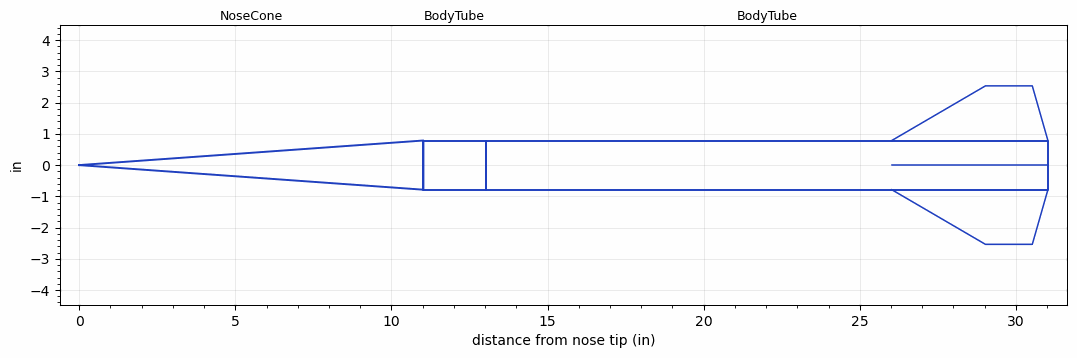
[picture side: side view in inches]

<RASAeroDocument>
 <FileVersion>2</FileVersion>
 <RocketDesign>
  <NoseCone>
   <Length>11.025</Length>
   <Diameter>1.575</Diameter>
   <Shape>Conical</Shape>
   <BluntRadius>0.065</BluntRadius>
   <Location>0</Location>
  </NoseCone>
  <BodyTube>
   <Length>2</Length>
   <Diameter>1.575</Diameter>
   <Location>11.025</Location>
  </BodyTube>
  <BodyTube>
   <Length>18</Length>
   <Diameter>1.575</Diameter>
   <Location>13.025</Location>
   <Fin>
    <Count>4</Count>
    <Chord>5</Chord>
    <Span>1.75</Span>
    <SweepDistance>3</SweepDistance>
    <TipChord>1.5</TipChord>
    <Thickness>0.1181</Thickness>
    <LERadius>0.065</LERadius>
    <Location>5</Location>
    <AirfoilSection>Hexagonal</AirfoilSection>
    <FX1>0.25</FX1>
    <FX3>0.25</FX3>
   </Fin>
   <Protuberance>
    <StreamlinedNoBaseDrag>0</StreamlinedNoBaseDrag>
    <StreamlinedWithBaseDrag>0.18</StreamlinedWithBaseDrag>
    <InclinedPlate1Angle>0</InclinedPlate1Angle>
    <InclinedPlate1FrontalArea>0</InclinedPlate1FrontalArea>
    <InclinedPlate2Angle>0</InclinedPlate2Angle>
    <InclinedPlate2FrontalArea>0</InclinedPlate2FrontalArea>
   </Protuberance>
  </BodyTube>
  <Surface>Smooth Paint</Surface>
  <ModifiedBarrowman>True</ModifiedBarrowman>
  <Turbulence>True</Turbulence>
  <UseBooster1>False</UseBooster1>
  <UseBooster2>False</UseBooster2>
 </RocketDesign>
 <LaunchSite>
  <Altitude>4300</Altitude>
  <Pressure>25.85</Pressure>
  <RodAngle>3</RodAngle>
  <RodLength>4</RodLength>
  <Temperature>44.74</Temperature>
  <WindSpeed>4.47</WindSpeed>
 </LaunchSite>
 <Recovery>
  <Altitude1>656.168</Altitude1>
  <Altitude2>0</Altitude2>
  <DeviceType1>Parachute</DeviceType1>
  <DeviceType2>None</DeviceType2>
  <Event1>False</Event1>
  <Event2>False</Event2>
  <Size1>18</Size1>
  <Size2>0</Size2>
  <EventType1>Apogee</EventType1>
  <EventType2>None</EventType2>
  <CD1>0.8</CD1>
  <CD2>0</CD2>
 </Recovery>
 <SimulationList>
  <Simulation>
   <SustainerEngine>I540WT  (CTI)</SustainerEngine>
   <SustainerLaunchWt>2.1</SustainerLaunchWt>
   <SustainerNozzleDiameter>0.75</SustainerNozzleDiameter>
   <SustainerCG>21.26</SustainerCG>
   <SustainerIgnitionDelay>0</SustainerIgnitionDelay>
   <Booster1SeparationDelay>0</Booster1SeparationDelay>
   <Booster1IgnitionDelay>0</Booster1IgnitionDelay>
   <IncludeBooster1>False</IncludeBooster1>
   <Booster2Delay>0</Booster2Delay>
   <IncludeBooster2>False</IncludeBooster2>
   <TimetoApogee>21.8304</TimetoApogee>
   <MaxAltitude>12234.75</MaxAltitude>
   <MaxVelocity>2283.898</MaxVelocity>
  </Simulation>
 </SimulationList>
</RASAeroDocument>
